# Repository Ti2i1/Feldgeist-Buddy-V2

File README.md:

# Feldgeist Buddy V2

A small ESP32-S3-based handheld designed to be carried as a keychain. It has a round touchscreen, a six-axis IMU and a rechargeable battery. Planned applications include step counting, motion logging and simple games.

**Status:** Hardware Rev. A designed, not yet manufactured or tested.

| Front | Back |
| :---: | :---: |
|  |  |

*KiCad 3D renders. Some component models are missing.*

## Hardware

| Component | Specification |
| --- | --- |
| MCU | ESP32-S3-MINI-1-N4R2 |
| Memory | 4 MB flash, 2 MB PSRAM |
| IMU | LSM6DSV32XTR |
| Display | 1.28-inch IPS LCD, 240 × 240, GC9A01A |
| Touch controller | CST816D |
| Microphone | ZTS6117 |
| Battery | Single-cell LiPo, capacity TBD |
| Battery charger | BQ25185 |
| Voltage regulator | TPS631000, 3.3 V buck-boost |
| Connectivity | USB-C, Wi-Fi, BLE |
| PCB | Ø42.5 mm, 4 layers |

## PCB layout

| Front | Back |
| :---: | :---: |
|  |  |

<details>
<summary>Additional PCB views</summary>

| Front | Back |
| :---: | :---: |
|  |  |

</details>

## Schematics

<details>
<summary>Main schematic</summary>

</details>

<details>
<summary>MCU</summary>

</details>

<details>
<summary>Peripherals</summary>

</details>

<details>
<summary>Power supply</summary>

</details>

KiCad project files: [`Kicad/`](Kicad/).

## Development status

- [x] Rev. A schematic and PCB layout
- [ ] PCB fabrication and assembly
- [ ] Hardware testing
- [ ] Firmware
- [ ] 3D-printed enclosure

## Credits and license

PCB design: Ti2i1. Design feedback from the electronics community on Discord. AI-assisted research, troubleshooting and silkscreen artwork.

No project license has been selected. Third-party materials retain their respective licenses.

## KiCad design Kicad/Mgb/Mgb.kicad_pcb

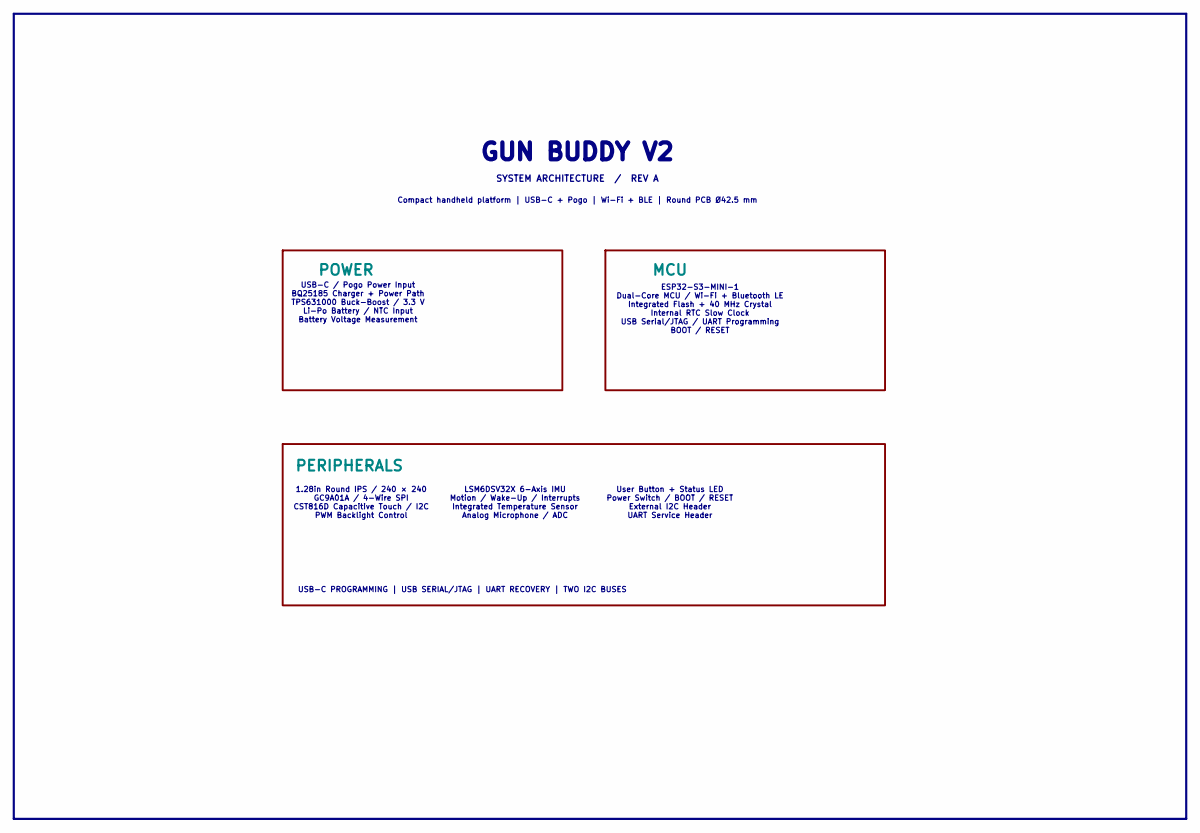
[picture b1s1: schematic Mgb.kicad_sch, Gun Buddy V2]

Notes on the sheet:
Compact handheld platform | USB-C + Pogo | Wi-Fi + BLE | Round PCB Ø42.5 mm
1.28in Round IPS / 240 × 240 GC9A01A / 4-Wire SPI CST816D Capacitive Touch / I2C PWM Backlight Control
GUN BUDDY V2
User Button + Status LED Power Switch / BOOT / RESET External I2C Header UART Service Header
USB-C PROGRAMMING | USB SERIAL/JTAG | UART RECOVERY | TWO I2C BUSES
ESP32-S3-MINI-1 Dual-Core MCU / Wi-Fi + Bluetooth LE Integrated Flash + 40 MHz Crystal Internal RTC Slow Clock USB Serial/JTAG / UART Programming BOOT / RESET
USB-C / Pogo Power Input BQ25185 Charger + Power Path TPS631000 Buck-Boost / 3.3 V Li-Po Battery / NTC Input Battery Voltage Measurement
SYSTEM ARCHITECTURE / REV A
LSM6DSV32X 6-Axis IMU Motion / Wake-Up / Interrupts Integrated Temperature Sensor Analog Microphone / ADC

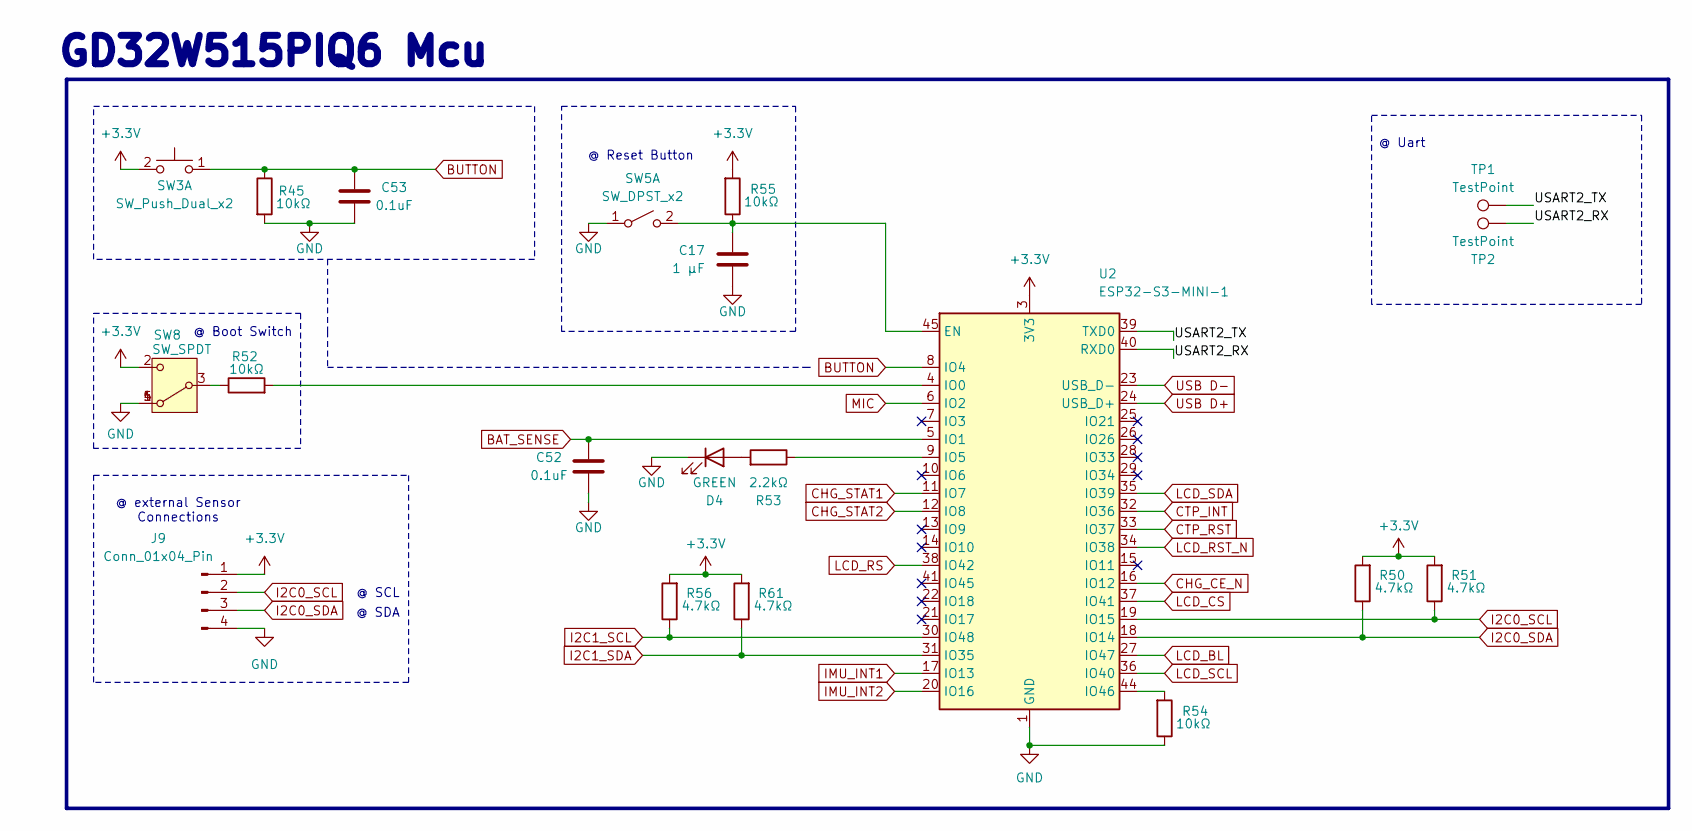
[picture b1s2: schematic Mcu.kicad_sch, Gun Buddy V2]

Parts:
C17: 1 µF; C_0402_1005Metric; JLCPCB Part # C52923
C52, C53: 0.1uF; C_0402_1005Metric
D4: GREEN; LED_0603_1608Metric; JLCPCB Part # C2289
J9: Conn_01x04_Pin; Hirose_DF13-04P-1.25DSA_1x04_P1.25mm_Vertical; JLCPCB Part # C2845522
R45, R52, R54, R55: 10kΩ; R_0402_1005Metric
R50, R51, R56, R61: 4.7kΩ; R_0402_1005Metric
R53: 2.2kΩ; R_0603_1608Metric
SW3: SW_Push_Dual_x2; SW-TH_L6.1-W5.0-P5.00; JLCPCB Part # C561491
SW5: SW_DPST_x2; SW_SPST_TS-1088-xR020; JLCPCB Part # C720477
SW8: SW_SPDT; SW-SMD_SSAJ110100; JLCPCB Part # C160863
TP1, TP2: TestPoint; TestPoint_Pad_D1.0mm
U2: ESP32-S3-MINI-1; ESP32-S2-MINI-1

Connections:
+3.3V: J9.1, R50.2, R51.2, R55.2, R56.2, R61.2, SW3.2 (D), SW8.2 (B), U2.3 (3V3); also elsewhere on the board
/MCU/USART2_RX: TP2.1 (1_1), U2.40 (RXD0)
/MCU/USART2_TX: TP1.1 (1_1), U2.39 (TXD0)
BAT_SENSE: C52.1, U2.5 (IO1); also elsewhere on the board
BUTTON: C53.1, R45.1, SW3.1 (C), U2.8 (IO4)
CHG_CE_N: U2.16 (IO12); also elsewhere on the board
CHG_STAT1: U2.11 (IO7); also elsewhere on the board
CHG_STAT2: U2.12 (IO8); also elsewhere on the board
CTP_INT: U2.32 (IO36); also elsewhere on the board
CTP_RST: U2.33 (IO37); also elsewhere on the board
GND: C17.2, C52.2, C53.2, D4.1 (K), J9.4, R45.2, R54.1, SW5.1 (A), SW8.1 (A), SW8.4 (C), SW8.5 (C), U2.1 (GND), U2.2 (GND), U2.42 (GND), U2.43 (GND), U2.46 (GND), U2.47 (GND), U2.48 (GND), U2.49 (GND), U2.50 (GND), U2.51 (GND), U2.52 (GND), U2.53 (GND), U2.54 (GND), U2.55 (GND), U2.56 (GND), U2.57 (GND), U2.58 (GND), U2.59 (GND), U2.60 (GND), U2.61 (GND), U2.62 (GND), U2.63 (GND), U2.64 (GND), U2.65 (GND); also elsewhere on the board
I2C0_SCL: J9.2, R51.1, U2.19 (IO15); also elsewhere on the board
I2C0_SDA: J9.3, R50.1, U2.18 (IO14); also elsewhere on the board
I2C1_SCL: R56.1, U2.30 (IO48); also elsewhere on the board
I2C1_SDA: R61.1, U2.31 (IO35); also elsewhere on the board
IMU_INT1: U2.17 (IO13); also elsewhere on the board
IMU_INT2: U2.20 (IO16); also elsewhere on the board
LCD_BL: U2.27 (IO47); also elsewhere on the board
LCD_CS: U2.37 (IO41); also elsewhere on the board
LCD_RS: U2.38 (IO42); also elsewhere on the board
LCD_RST_N: U2.34 (IO38); also elsewhere on the board
LCD_SCL: U2.36 (IO40); also elsewhere on the board
LCD_SDA: U2.35 (IO39); also elsewhere on the board
MIC: U2.6 (IO2); also elsewhere on the board
unnamed: D4.2 (A), R53.2
unnamed: R52.1, SW8.3 (C)
unnamed: C17.1, R55.1, SW5.2 (B), U2.45 (EN)
unnamed: R52.2, U2.4 (IO0)
unnamed: R53.1, U2.9 (IO5)
unnamed: R54.2, U2.44 (IO46)
USB D+: U2.24 (USB_D+); also elsewhere on the board
USB D-: U2.23 (USB_D-); also elsewhere on the board

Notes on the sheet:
@ SDA
@ Reset Button
@ SCL
@ external Sensor Connections
@ Uart
@ Boot Switch
GD32W515PIQ6 Mcu

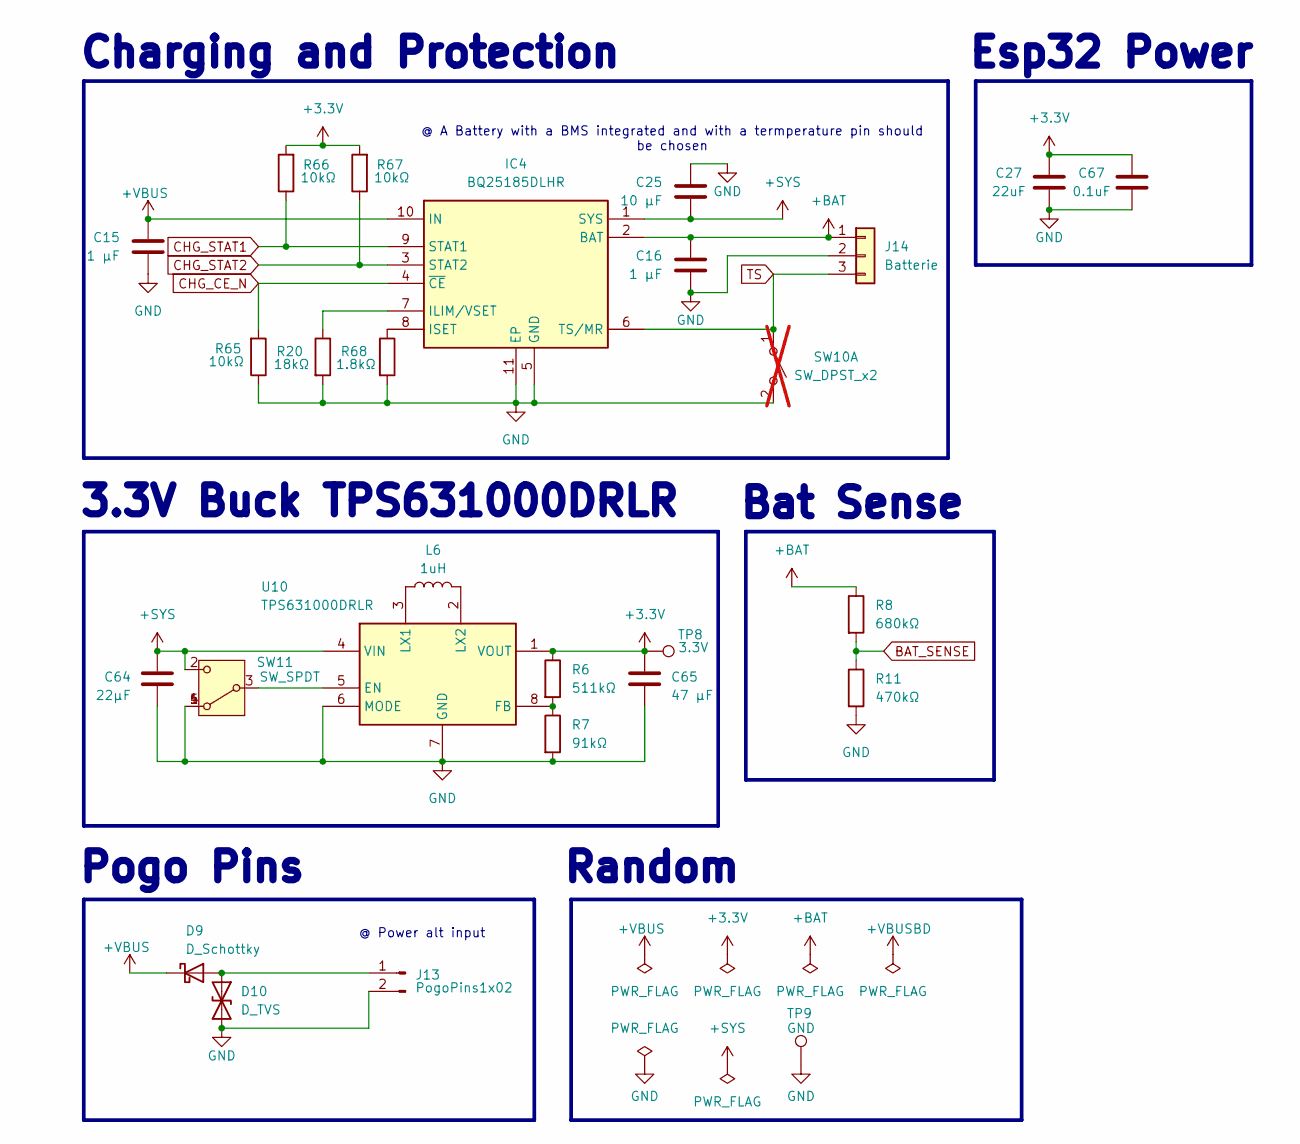
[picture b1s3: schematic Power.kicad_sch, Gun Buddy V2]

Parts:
C15, C16: 1 µF; C_0402_1005Metric; JLCPCB Part # C52923
C25: 10 µF; C_0603_1608Metric; JLCPCB Part # C96446
C27: 22uF; C_0603_1608Metric
C64: 22µF; C_0805_2012Metric; JLCPCB Part # C45783
C65: 47 µF; C_1206_3216Metric; JLCPCB Part # C96123
C67: 0.1uF; C_0402_1005Metric
D9: D_Schottky; D_SOD-123; JLCPCB Part # C8598
D10: D_TVS; ESD441DPLR; JLCPCB Part # C22427765
IC4: BQ25185DLHR; SON40P220X200X80-11N; Mouser Part Number 595-BQ25185DLHR
J13: PogoPins1x02
J14: Batterie; PinHeader_1x03_P2.00mm_Vertical
L6: 1uH; L_1008_2520Metric; JLCPCB Part # C1882521
R6: 511kΩ; R_0603_1608Metric
R7: 91kΩ; R_0603_1608Metric
R8: 680kΩ; R_0603_1608Metric
R11: 470kΩ; R_0603_1608Metric
R20: 18kΩ; R_0603_1608Metric
R65, R66, R67: 10kΩ; R_0402_1005Metric
R68: 1.8kΩ; R_0402_1005Metric
SW10: SW_DPST_x2; SW_SPST_TS-1088-xR020; JLCPCB Part # C720477; not fitted
SW11: SW_SPDT; SW-SMD_SSAJ110100; JLCPCB Part # C160863
TP8: 3.3V; TestPoint_Pad_D2.0mm
TP9: GND; TestPoint_Pad_D2.0mm
U10: TPS631000DRLR; SOTFL50P160X60-8N; Mouser Part Number 595-TPS631000DRLR

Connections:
+3.3V: C27.1, C65.1, C67.1, R6.1, R66.2, R67.2, TP8.1 (1_1), U10.1 (VOUT); also elsewhere on the board
+BAT: C16.1, IC4.2 (BAT), J14.1, R8.1
+SYS: C25.2, C64.1, IC4.1 (SYS), SW11.2 (B), U10.4 (VIN)
+VBUS: C15.1, D9.1 (K), IC4.10 (IN); also elsewhere on the board
BAT_SENSE: R8.2, R11.1; also elsewhere on the board
CHG_CE_N: IC4.4 (~CE), R65.2; also elsewhere on the board
CHG_STAT1: IC4.9 (STAT1), R66.1; also elsewhere on the board
CHG_STAT2: IC4.3 (STAT2), R67.1; also elsewhere on the board
GND: C15.2, C16.2, C25.1, C27.2, C64.2, C65.2, C67.2, D10.2 (A2), IC4.5 (GND), IC4.11 (EP), J13.2, J14.2, R7.2, R11.2, R20.2, R65.1, R68.2, SW10.2 (B), SW11.1 (A), SW11.4 (C), SW11.5 (C), TP9.1 (1_1), U10.6 (MODE), U10.7 (GND); also elsewhere on the board
unnamed: D9.2 (A), D10.1 (A1), J13.1
unnamed: IC4.7 (ILIM/VSET), R20.1
unnamed: IC4.8 (ISET), R68.1
unnamed: SW11.3 (C), U10.5 (EN)
unnamed: R6.2, R7.1, U10.8 (FB)
unnamed: L6.1, U10.3 (LX1)
unnamed: L6.2, U10.2 (LX2)
TS: IC4.6 (TS/MR), J14.3, SW10.1 (A)

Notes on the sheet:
Bat Sense
Random
Charging and Protection
Esp32 Power
@ Power alt input
@ A Battery with a BMS integrated and with a termperature pin should be chosen
Pogo Pins
3.3V Buck TPS631000DRLR

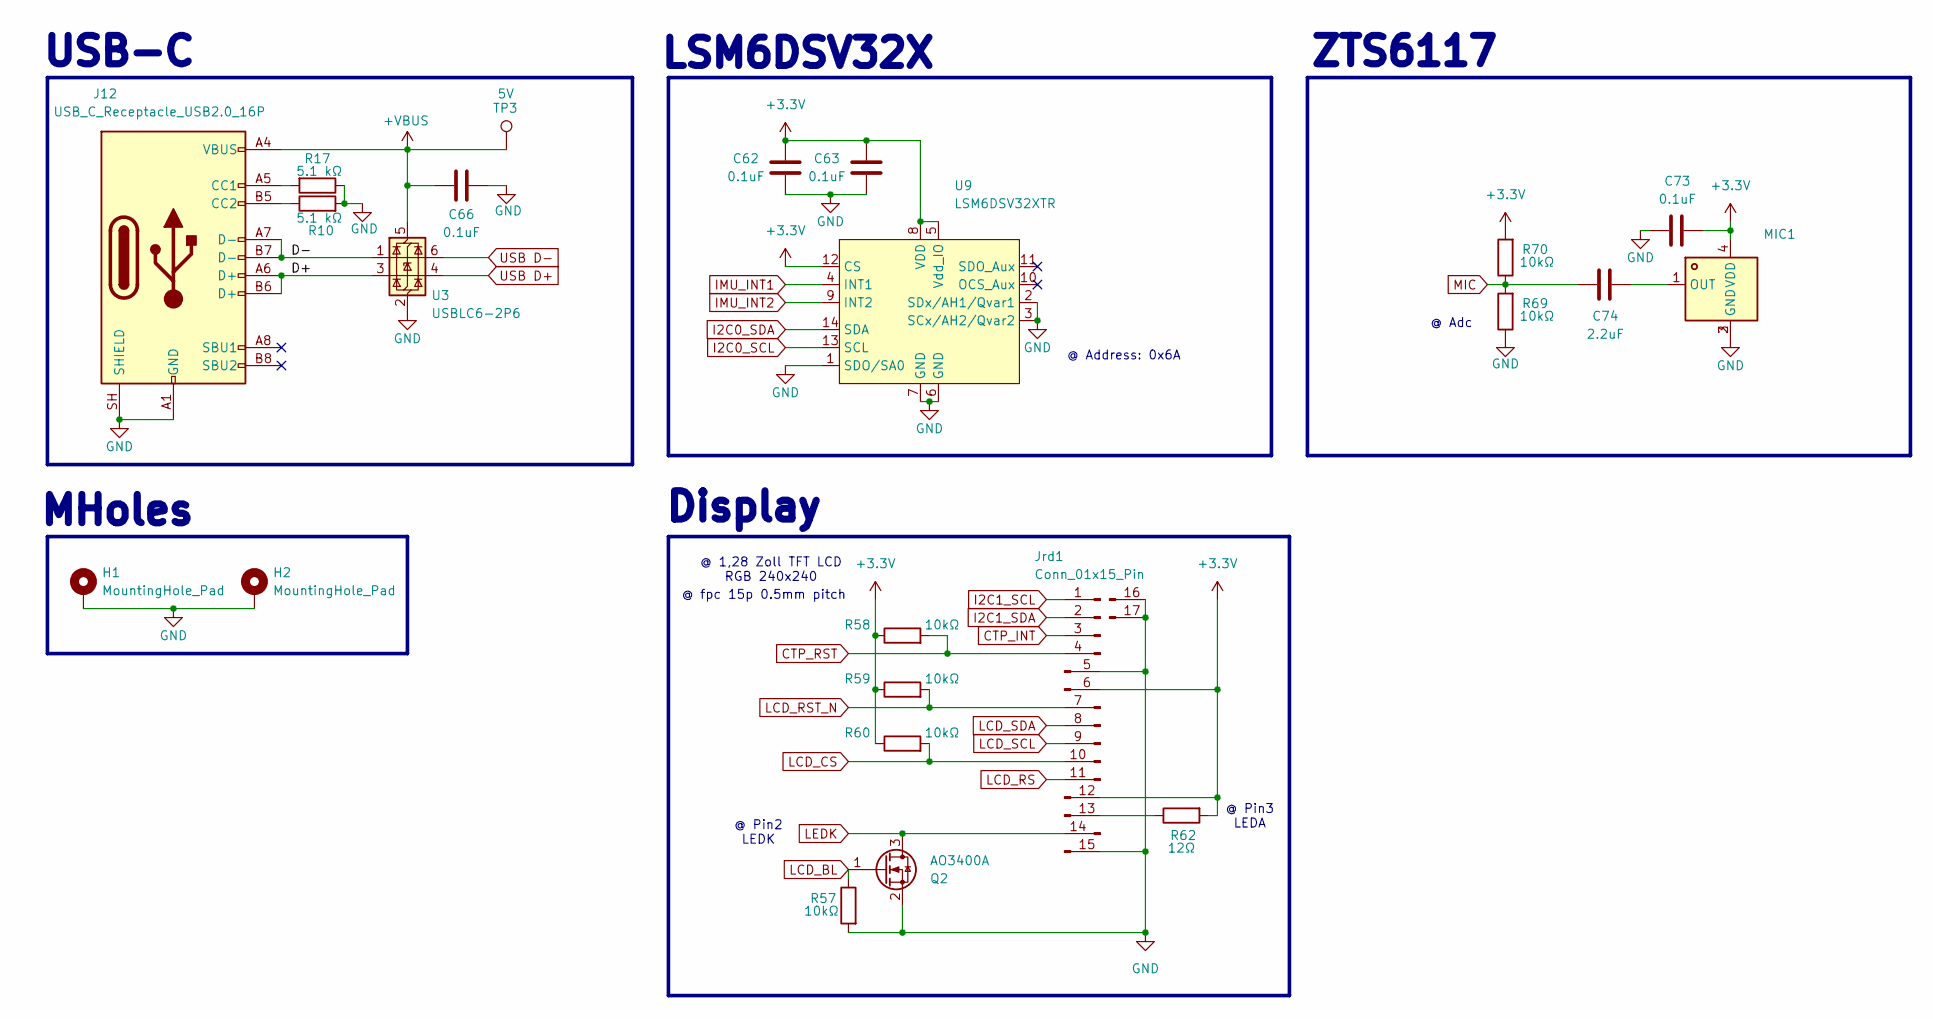
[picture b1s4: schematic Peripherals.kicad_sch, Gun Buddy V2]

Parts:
C62, C63, C66, C73: 0.1uF; C_0402_1005Metric
C74: 2.2uF; C_0402_1005Metric
H1, H2: MountingHole_Pad; MountingHole_2.2mm_M2_DIN965_Pad
J12: USB_C_Receptacle_USB2.0_16P; USB_C_Receptacle_JAE_DX07S016JA1R1500
Jrd1: Conn_01x15_Pin; FPC-SMD_AFC07-S15ECA-00; JLCPCB Part # C262588
MIC1: MIC-SMD_4P-L2.8-W1.9-P1.84-TL_ZTS6117; Manufacturer Part ZTS6117; LCSC Part Name 1.5V~3.6V42dB
Q2: AO3400A; SOT-23
R10, R17: 5.1 kΩ; R_0603_1608Metric; JLCPCB Part # C23186
R57, R58, R59, R60, R69, R70: 10kΩ; R_0402_1005Metric
R62: 12Ω; R_0402_1005Metric
TP3: 5V; TestPoint_Pad_D2.0mm
U3: USBLC6-2P6; SOT-666
U9: LSM6DSV32XTR; LGA-14_3x2.5mm_P0.5mm_LayoutBorder3x4y

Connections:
+3.3V: C62.1, C63.1, C73.1, Jrd1.6, Jrd1.12, MIC1.4 (VDD), R58.1, R59.1, R60.1, R62.2, R70.2, U9.5 (Vdd_IO), U9.8 (VDD), U9.12 (CS); also elsewhere on the board
+VBUS: C66.1, J12.A4 (VBUS), J12.A9 (VBUS), J12.B4 (VBUS), J12.B9 (VBUS), TP3.1 (1_1), U3.5 (VBUS); also elsewhere on the board
/PERIPHERALS/D+: J12.A6 (D+), J12.B6 (D+), U3.3 (I/O2)
/PERIPHERALS/D-: J12.A7 (D-), J12.B7 (D-), U3.1 (I/O1)
CTP_INT: Jrd1.3; also elsewhere on the board
CTP_RST: Jrd1.4, R58.2; also elsewhere on the board
GND: C62.2, C63.2, C66.2, C73.2, H1.1 (1_1), H2.1 (1_1), J12.A1 (GND), J12.A12 (GND), J12.B1 (GND), J12.B12 (GND), J12.SH (SHIELD), Jrd1.5, Jrd1.15, Jrd1.16 (MP1), Jrd1.17 (MP2), MIC1.2 (GND), MIC1.3 (GND), Q2.2 (S), R10.2, R17.1, R57.2, R69.1, U3.2 (GND), U9.1 (SDO/SA0), U9.2 (SDx/AH1/Qvar1), U9.3 (SCx/AH2/Qvar2), U9.6 (GND), U9.7 (GND); also elsewhere on the board
I2C0_SCL: U9.13 (SCL); also elsewhere on the board
I2C0_SDA: U9.14 (SDA); also elsewhere on the board
I2C1_SCL: Jrd1.1; also elsewhere on the board
I2C1_SDA: Jrd1.2; also elsewhere on the board
IMU_INT1: U9.4 (INT1); also elsewhere on the board
IMU_INT2: U9.9 (INT2); also elsewhere on the board
LCD_BL: Q2.1 (G), R57.1; also elsewhere on the board
LCD_CS: Jrd1.10, R60.2; also elsewhere on the board
LCD_RS: Jrd1.11; also elsewhere on the board
LCD_RST_N: Jrd1.7, R59.2; also elsewhere on the board
LCD_SCL: Jrd1.9; also elsewhere on the board
LCD_SDA: Jrd1.8; also elsewhere on the board
LEDK: Jrd1.14, Q2.3 (D)
MIC: C74.1, R69.2, R70.1; also elsewhere on the board
unnamed: J12.A5 (CC1), R17.2
unnamed: J12.B5 (CC2), R10.1
unnamed: Jrd1.13, R62.1
unnamed: C74.2, MIC1.1 (OUT)
USB D+: U3.4 (I/O2); also elsewhere on the board
USB D-: U3.6 (I/O1); also elsewhere on the board

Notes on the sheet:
USB-C
Display
ZTS6117
@ 1,28 Zoll TFT LCD RGB 240x240
@ Pin3 LEDA
@ Adc
@ Address: 0x6A
MHoles
LSM6DSV32X
@ fpc 15p 0.5mm pitch
@ Pin2 LEDK

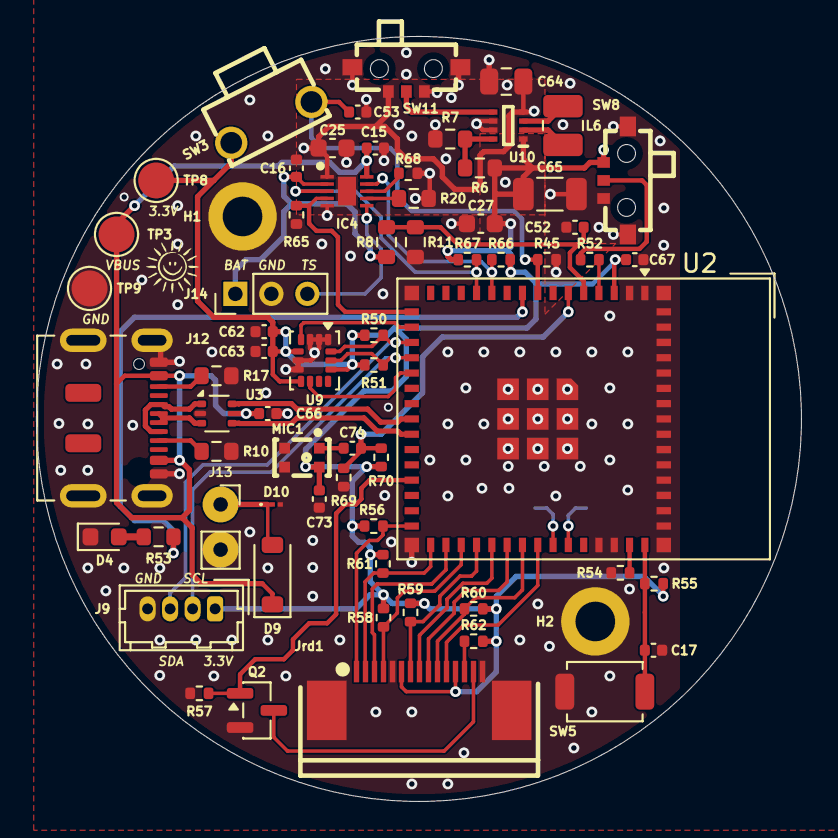
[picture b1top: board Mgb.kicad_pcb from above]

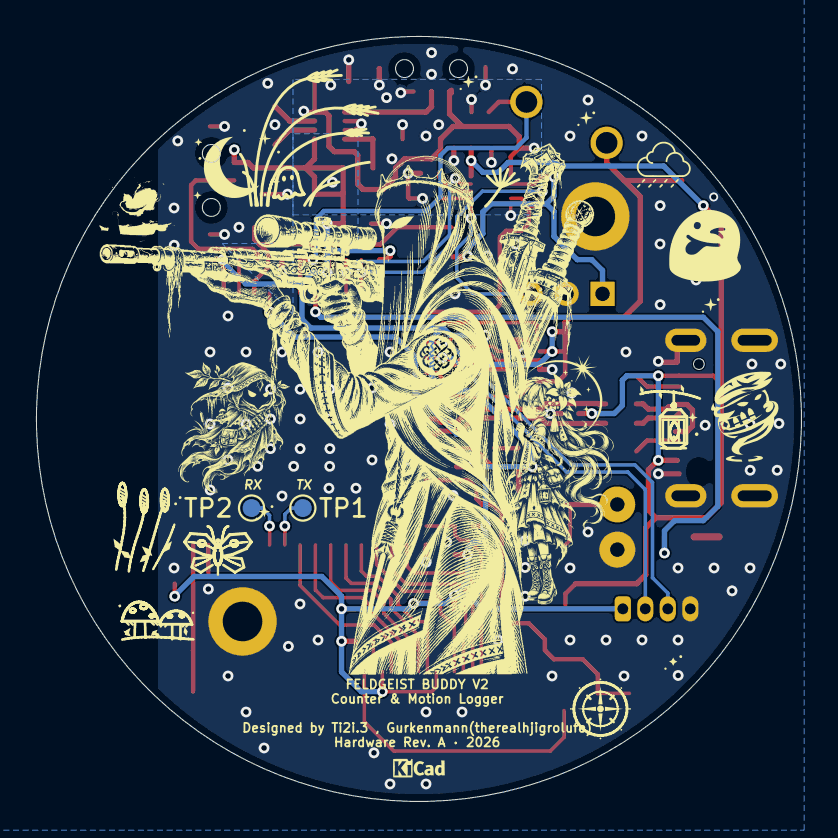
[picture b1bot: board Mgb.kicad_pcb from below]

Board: 4 copper layers, 42.5 x 42.5 mm, 69 parts (2 on the bottom side), 50 nets.
